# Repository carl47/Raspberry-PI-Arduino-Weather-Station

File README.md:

# Raspberry-PI-Arduino-Weather-Station

Raspberry Pi used for TV display and data storage

Indoor Arduino used for Temp/Humid, IR receiver and
communication with outdoor Arduino

Outdoor Arduino used for Temp/Humid, rainfall, wind and lightning

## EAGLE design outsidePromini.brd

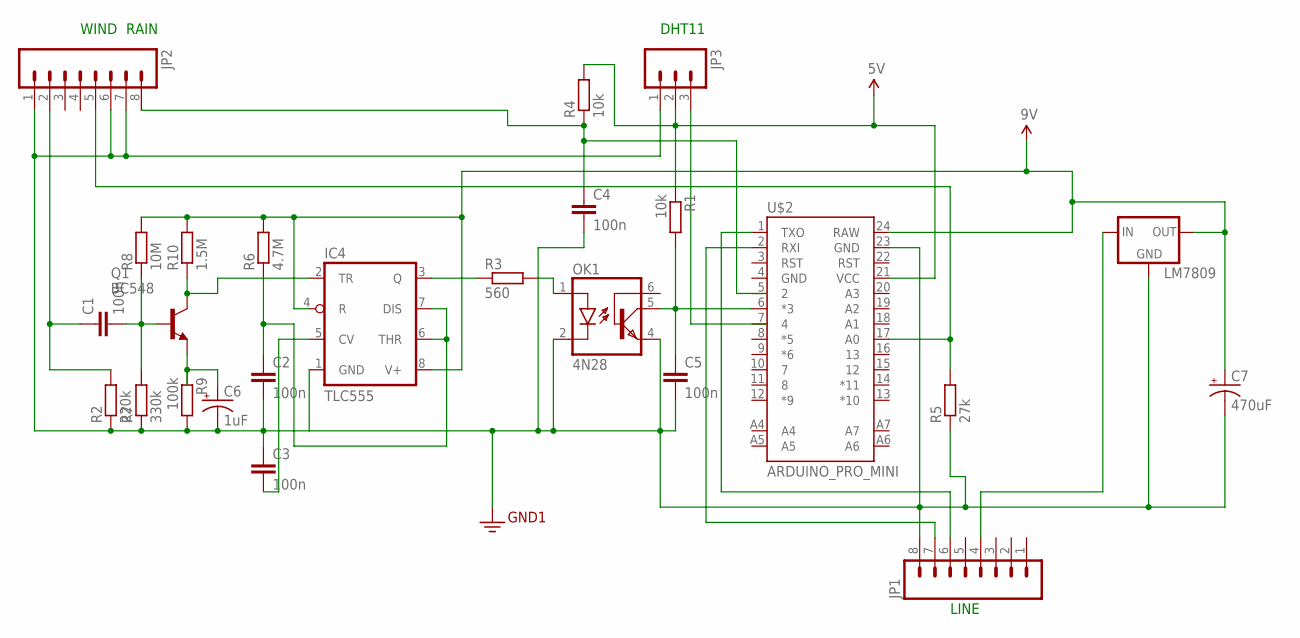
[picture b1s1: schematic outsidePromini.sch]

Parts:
C1, C2, C3, C4, C5: 100n; CAP-PTH-SMALL-KIT
C6: 1uF; CPOL-RADIAL-100UF-25V
C7: 470uF; CPOL-RADIAL-100UF-25V
IC4: TLC555; DIL08
JP1, JP2: M08LOCK_LONGPADS; 1X08_LOCK_LONGPADS
JP3: M03LOCK_LONGPADS; 1X03_LOCK_LONGPADS
LM7809: 78XXS
OK1: 4N28; DIL06
Q1: BC548; TO92-EBC
R1, R4: 10k; 0204/5
R2: 220k; 0204/5
R3: 560; 0204/5
R5: 27k; 0204/5
R6: 4.7M; 0204/5
R7: 330k; 0204/5
R8: 10M; 0204/5
R9: 100k; 0204/5
R10: 1.5M; 0204/5
U$2: ARDUINO_PRO_MINI

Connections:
3.3V: C2.2, C3.1, C4.2, C5.2, C6.2 (-), C7.2 (-), IC4.1 (GND), JP1.8, JP2.1, JP2.6, JP2.7, JP3.1, LM7809.GND, OK1.2 (C), OK1.4 (EMI), R2.1, R5.1, R7.1, R9.2, U$2.23 (GND)
5V: C7.1 (+), IC4.4 (R), IC4.8 (V+), JP3.2, LM7809.OUT, R1.1, R4.2, R6.2, R8.2, R10.2, U$2.21 (VCC), U$2.24 (RAW)
unnamed: C1.1, JP2.2, R2.2
unnamed: C1.2, Q1.B, R7.2, R8.1
unnamed: C6.1 (+), Q1.E, R9.1
unnamed: C2.1, IC4.6 (THR), IC4.7 (DIS), R6.1
unnamed: IC4.2 (TR), Q1.C, R10.1
unnamed: IC4.3 (Q), R3.1
unnamed: C3.2, IC4.5 (CV)
unnamed: OK1.1 (A), R3.2
unnamed: JP1.4, LM7809.IN
unnamed: JP1.7, U$2.2 (RXI)
unnamed: JP1.6, U$2.1 (TXO)
unnamed: C5.1, OK1.5 (COL), R1.2, U$2.6 (*3)
unnamed: C4.1, JP2.8, R4.1
unnamed: JP2.5, R5.2, U$2.17 (A0)

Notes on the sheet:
DHT11
RAIN
WIND
LINE

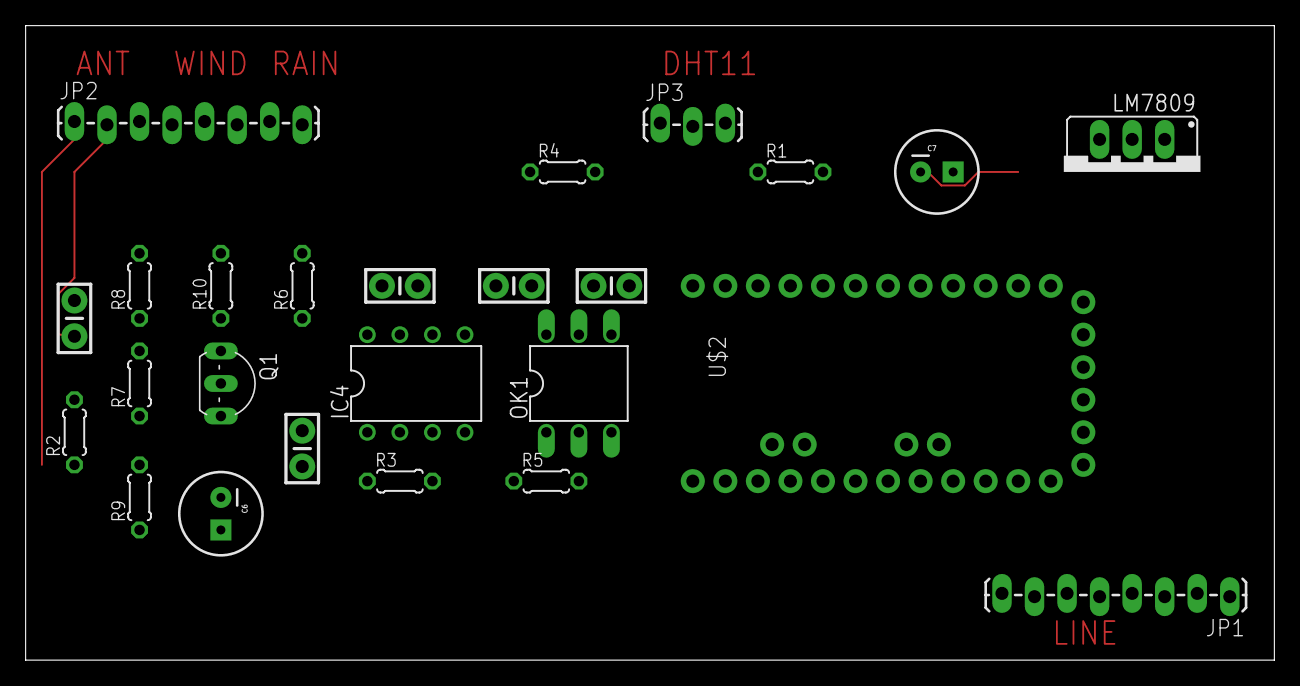
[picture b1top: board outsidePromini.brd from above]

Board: 2 copper layers, 97.5 x 49.5 mm, 25 parts (0 on the bottom side), 16 nets.

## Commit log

2020-12-12 Add files via upload
    code using arduino Pro mini
2020-12-17 Add files via upload
    use arduino pro mini
2021-01-09 Add files via upload
    better wind speed

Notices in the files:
parts and their libraries:
SparkFun-Boards: Licensing: Creative Commons ShareAlike 4.0 International - https://creativecommons.org/licenses/by-sa/4.0
